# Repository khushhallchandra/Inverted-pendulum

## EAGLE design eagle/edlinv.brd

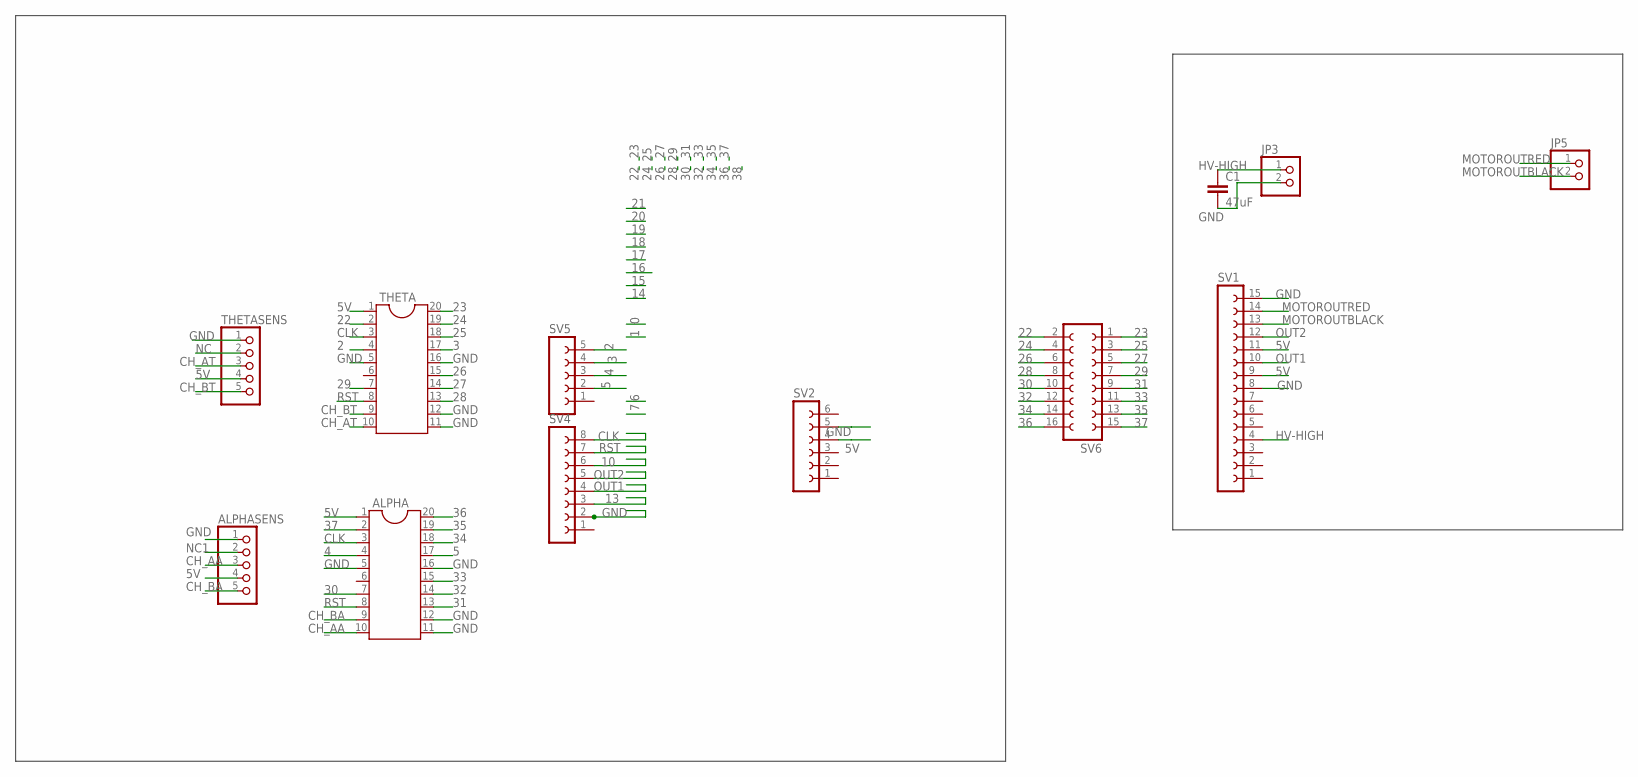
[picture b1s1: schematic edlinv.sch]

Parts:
ALPHA: DIL20
ALPHASENS: PINHD-1X5; 1X05
C1: 47uF; C025-025X050
JP3, JP5: PINHD-1X2; 1X02
SV1: FE15-1; FE15
SV2: FE06-1; FE06
SV4: FE08-1; FE08
SV5: FE05-1
SV6: FE08-2
THETA: DIL20
THETASENS: PINHD-1X5; 1X05

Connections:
2: SV5.5, THETA.4
3: SV5.4, THETA.17
4: ALPHA.4, SV5.3
5: ALPHA.17, SV5.2
5V: ALPHA.1, ALPHASENS.4, SV1.9, SV1.11, SV2.4, THETA.1, THETASENS.4
10: SV4.6
13: SV4.3
22: SV6.2, THETA.2
23: SV6.1, THETA.20
24: SV6.4, THETA.19
25: SV6.3, THETA.18
26: SV6.6, THETA.15
27: SV6.5, THETA.14
28: SV6.8, THETA.13
29: SV6.7, THETA.7
30: ALPHA.7, SV6.10
31: ALPHA.13, SV6.9
32: ALPHA.14, SV6.12
33: ALPHA.15, SV6.11
34: ALPHA.18, SV6.14
35: ALPHA.19, SV6.13
36: ALPHA.20, SV6.16
37: ALPHA.2, SV6.15
CH_AA: ALPHA.10, ALPHASENS.3
CH_AT: THETA.10, THETASENS.3
CH_BA: ALPHA.9, ALPHASENS.5
CH_BT: THETA.9, THETASENS.5
CLK: ALPHA.3, SV4.8, THETA.3
GND: ALPHA.5, ALPHA.11, ALPHA.12, ALPHA.16, ALPHASENS.1, C1.2, JP3.2, SV1.8, SV1.15, SV2.5, SV4.2, THETA.5, THETA.11, THETA.12, THETA.16, THETASENS.1
HV-HIGH: C1.1, JP3.1, SV1.4
MOTOROUTBLACK: JP5.2, SV1.13
MOTOROUTRED: JP5.1, SV1.14
NC: THETASENS.2
NC1: ALPHASENS.2
OUT1: SV1.10, SV4.4
OUT2: SV1.12, SV4.5
RST: ALPHA.8, SV4.7, THETA.8

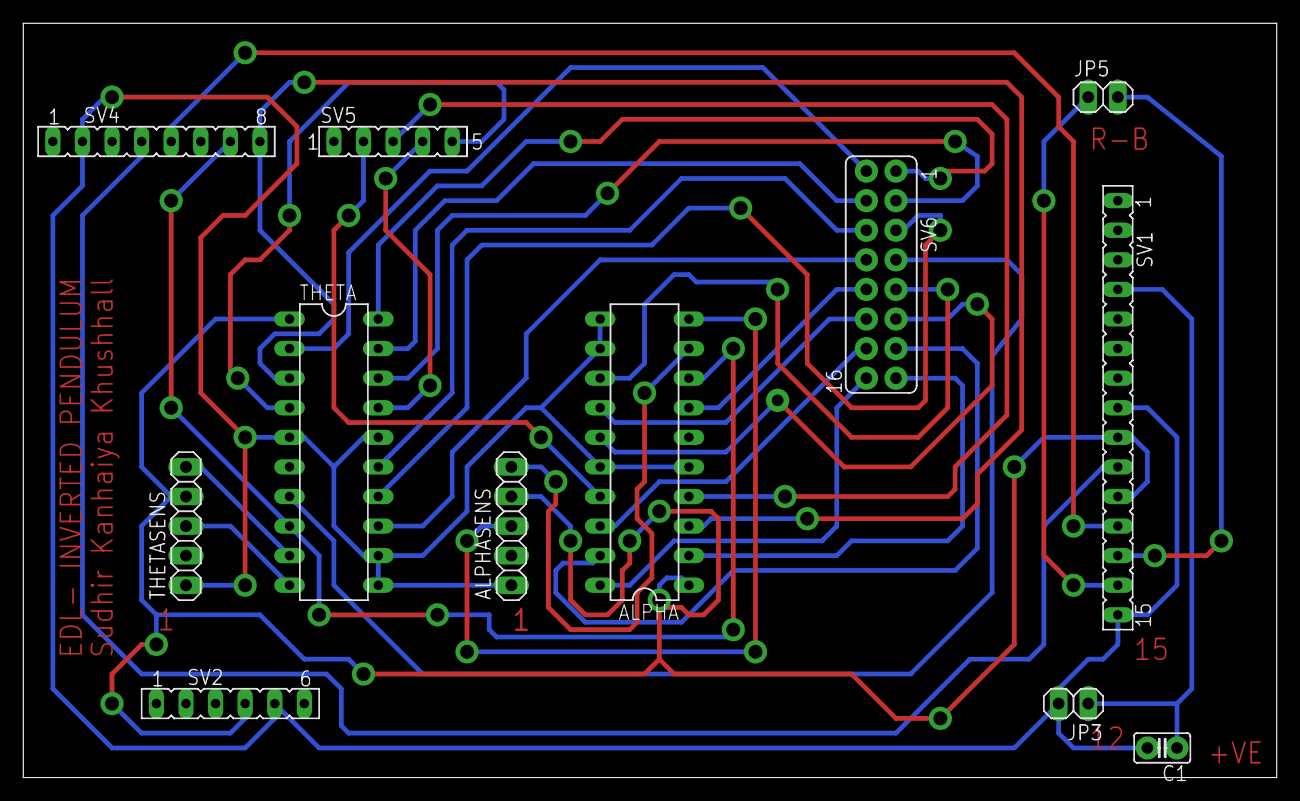
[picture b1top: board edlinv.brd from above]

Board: 2 copper layers, 107.6 x 64.8 mm, 12 parts (0 on the bottom side), 33 nets.

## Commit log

2016-03-08 LQR implementation. Increased the speed of interrupt
2016-03-21 Some changes left
2016-04-14 Added PCB layout
2016-04-17 Added report
2016-04-25 Added data files
